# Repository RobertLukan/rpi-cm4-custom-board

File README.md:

Based on my previous projects I needed a customized RPI4 carrier board with 2 cameras input. The initial idea was taken from this project: https://www.tindie.com/products/dronecz/minimal-carrier-board-for-compute-module-4/.

I made several changes such as 4-layer PCB, added second camera lanes, differential routing for both cameras and HDMI, added temperature sensor, and added I2C and UART connectors.

I have added also two jumpers that allow disabling wireless and Bluetooth. I have tested nearly every connection. SD card connector does not work if you are using RPI4CM with emmc, otherwise, it should(not the fault of this design but the RPI design decision that I was not aware of while making this board)

In general, I am quite happy with the setup. JLCPCB manufactured and assembled most of the parts. However, one board did not have Hirose connectors soldered properly, I have received a coupon. I have not touched the spacing for Hirose connectors, but I found it may be slightly off. It is hard to connect RPI for the first time. But I don't want to modify it as it has been working for several weeks.

USB connector can be used to connect external devices. To flash a CM the dedicated jumper(OTG) needs to be connected . It is just USB2.0 and it is not delivering any power. I have tested powered USB hub/docking station and it is working fine. In this way even Ethernet connection can be used (again being limited to USB2.0)

I also created 3D-printed housing. It is my first 3d design of this type/scale, but it works. It does not have cutouts for HDMI and USB2.0 as I dont need them.

In order to use both cameras, config.txt file has to include both overlays as defined below, for my two cameras:

dtparam=i2c_arm=on

dtoverlay=imx708,cam0

dtoverlay=imx477,cam1

The majority of the connectors were assembled by JLCPCB(without I2C and camera connectors - not available at that time), I have included the production directory where all the details are attached. The positions of parts are not 100% aligned, so make sure if you are asking JLCPCB to assemble parts to align them correctly. It is very important to order the correct camera connector: https://www.digikey.at/en/products/detail/amphenol-cs-fci/SFW15R-1STAE1LF/4270877

I made several design decisions that suited my needs, such as different GPIO header connector, and 4-pin Groove connectors for UART and I2C, so they might not be suitable for your needs.

One important detail, I am powering this board with the Raspberry Pi power supply. Other power supplies with USB C connector might not work as RPI requires quite some power and I would need to implement USB PD.

Update:
I needed power(5V) for an external USB device. I knew that I could connect a powered USB docking station(hub), however, that requires yet another power supply. As I just needed to power the USB microphone, that was an overkill. I looked at my diagram and I noticed that I can take 5V from GPIO and connect one of the pins at the OTG jumper(as shown below). An important detail is that the track is not designed to carry a lot of current, so be reasonable. 

License:
Please feel free to use the design. Released under the following license: 
https://ohwr.org/cern_ohl_p_v2.txt

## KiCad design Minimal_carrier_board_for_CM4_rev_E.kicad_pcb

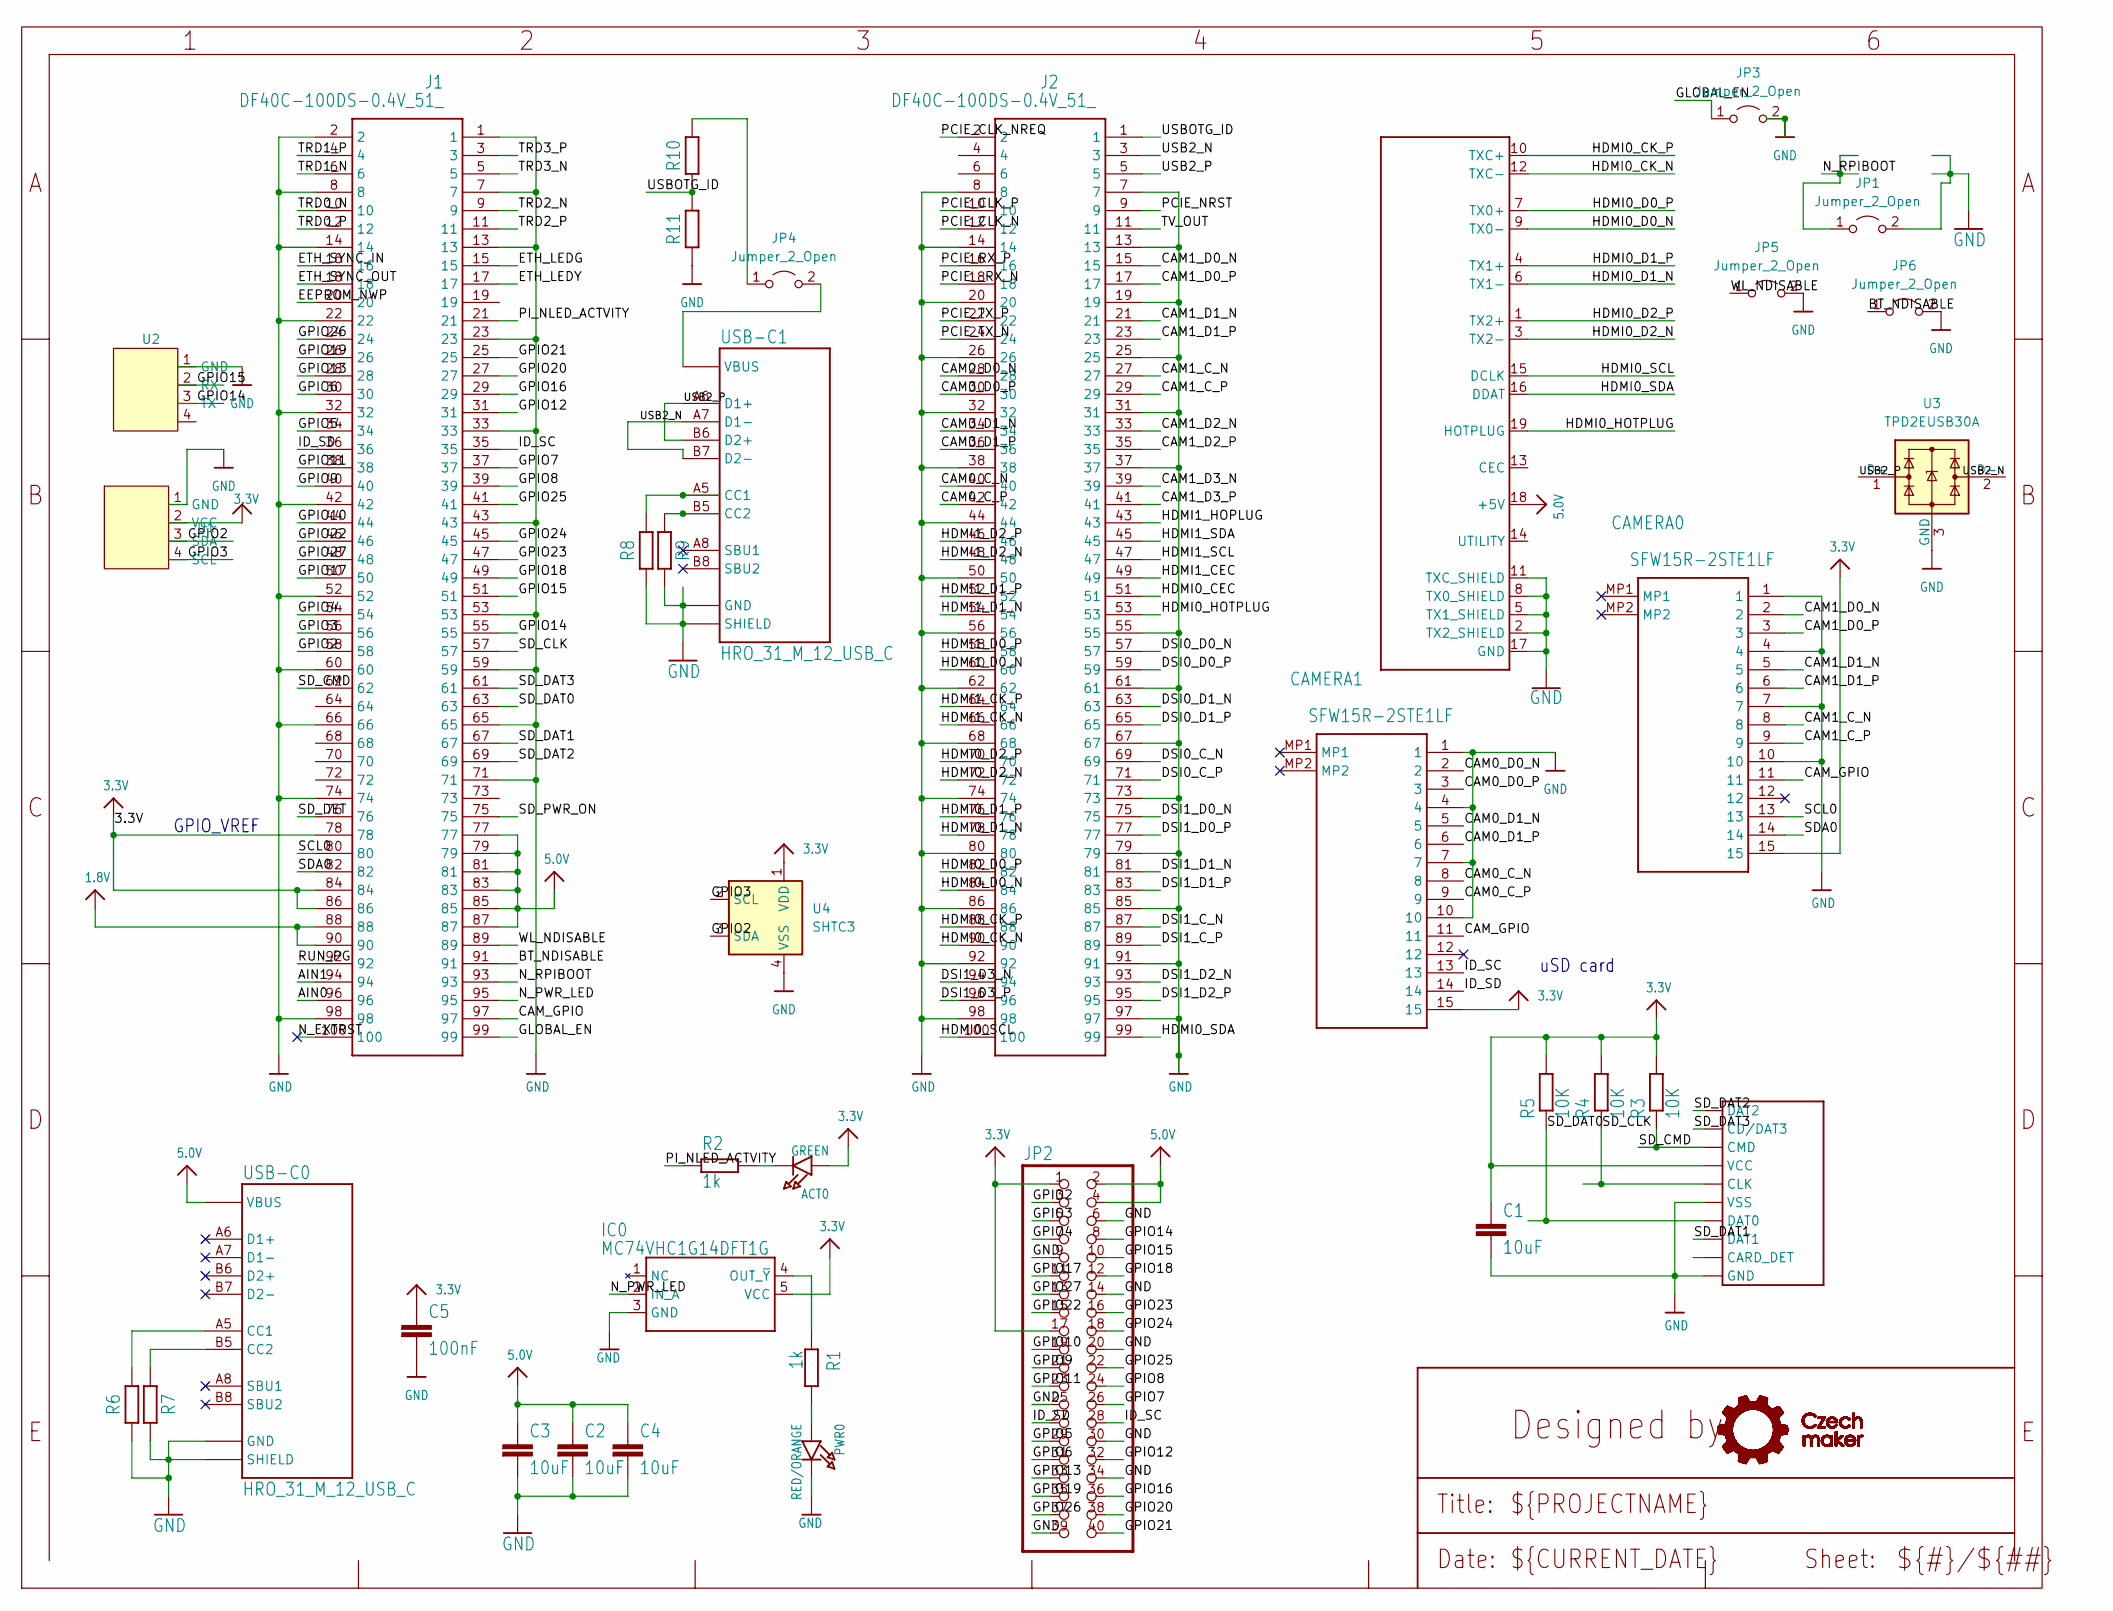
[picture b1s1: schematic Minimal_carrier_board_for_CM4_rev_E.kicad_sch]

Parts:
ACT0: GREEN; CHIPLED_0805_NOOUTLINE
C1, C2, C3, C4: 10uF; C0805
C5: 100nF; C0805
CAMERA0, CAMERA1: SFW15R-2STE1LF; SFW15R2STE1LF
HDMI0: HDMI_MOLEX_47151-0001; LCSC C428484
IC0: MC74VHC1G14DFT1G; SOT65P210X110-5N
J1: DF40C-100DS-0.4V_51_; DF40C100DS04V51; LCSC DF40C-100DS-0.4V(51)
J2: DF40C-100DS-0.4V_51_; DF40C100DS04V51
JP1, JP3, JP4, JP5, JP6: Jumper_2_Open; PinHeader_1x02_P2.54mm_Vertical
JP2: PINHD-2X20; 2X20
PWR0: RED/ORANGE; CHIPLED_0805_NOOUTLINE
R1, R2: 1k; R0805
R3, R4, R5: 10K; R0805
R6, R7, R8, R9: 5.1k; R0805
R10, R11: 2.2k; R0805
SD_CARD0: MICRO_SD_CARD_; TFP09-2--12B
U1, U2: NS-Tech_Grove_1x04_P2mm_Vertical
U3: TPD2EUSB30A; Texas_DRT-3
U4: SHTC3; Sensirion_DFN-4-1EP_2x2mm_P1mm_EP0.7x1.6mm
USB-C0, USB-C1: HRO_31_M_12_USB_C

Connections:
1.8V: J1.88, J1.90
3.3V: ACT0.A, C1.1, C5.1, CAMERA0.15, CAMERA1.15, IC0.5 (VCC), J1.78, J1.84, J1.86, JP2.1, JP2.17, R3.2, R4.2, R5.2, SD_CARD0.VCC, U1.2 (VCC), U4.1 (VDD); also elsewhere on the board
5.0V: C2.1, C3.1, C4.1, HDMI0.18 (+5V), J1.77, J1.79, J1.81, J1.83, J1.85, J1.87, JP2.2, JP2.4, USB-C0.A4 (VBUS), USB-C0.A9 (VBUS), USB-C0.B4 (VBUS), USB-C0.B9 (VBUS); also elsewhere on the board
/AIN0: J1.96
/AIN1: J1.94
/BT_NDISABLE: J1.91, JP6.1 (A)
/CAM0_C_N: CAMERA1.8, J2.40; also elsewhere on the board
/CAM0_C_P: CAMERA1.9, J2.42; also elsewhere on the board
/CAM0_D0_N: CAMERA1.2, J2.28; also elsewhere on the board
/CAM0_D0_P: CAMERA1.3, J2.30; also elsewhere on the board
/CAM0_D1_N: CAMERA1.5, J2.34; also elsewhere on the board
/CAM0_D1_P: CAMERA1.6, J2.36; also elsewhere on the board
/CAM1_C_N: CAMERA0.8, J2.27
/CAM1_C_P: CAMERA0.9, J2.29
/CAM1_D0_N: CAMERA0.2, J2.15
/CAM1_D0_P: CAMERA0.3, J2.17
/CAM1_D1_N: CAMERA0.5, J2.21
/CAM1_D1_P: CAMERA0.6, J2.23
/CAM1_D2_N: J2.33
/CAM1_D2_P: J2.35
/CAM1_D3_N: J2.39
/CAM1_D3_P: J2.41
/CAM_GPIO: CAMERA0.11, CAMERA1.11, J1.97; also elsewhere on the board
/DSI0_C_N: J2.69
/DSI0_C_P: J2.71
/DSI0_D0_N: J2.57
/DSI0_D0_P: J2.59
/DSI0_D1_N: J2.63
/DSI0_D1_P: J2.65
/DSI1_C_N: J2.87
/DSI1_C_P: J2.89
/DSI1_D0_N: J2.75
/DSI1_D0_P: J2.77
/DSI1_D1_N: J2.81
/DSI1_D1_P: J2.83
/DSI1_D2_N: J2.93
/DSI1_D2_P: J2.95
/DSI1_D3_N: J2.94
/DSI1_D3_P: J2.96
/EEPROM_NWP: J1.20
/ETH_LEDG: J1.15
/ETH_LEDY: J1.17
/ETH_SYNC_IN: J1.16
/ETH_SYNC_OUT: J1.18
/GLOBAL_EN: J1.99, JP3.1 (A)
/GPIO2: J1.58, JP2.3, U1.3 (SDA), U4.3 (SDA)
/GPIO3: J1.56, JP2.5, U1.4 (SCL), U4.2 (SCL)
/GPIO4: J1.54, JP2.7
/GPIO5: J1.34, JP2.29
/GPIO6: J1.30, JP2.31
/GPIO7: J1.37, JP2.26
/GPIO8: J1.39, JP2.24
/GPIO9: J1.40, JP2.21
/GPIO10: J1.44, JP2.19
/GPIO11: J1.38, JP2.23
/GPIO12: J1.31, JP2.32
/GPIO13: J1.28, JP2.33
/GPIO14: J1.55, JP2.8, U2.3 (TX)
/GPIO15: J1.51, JP2.10, U2.2 (RX)
/GPIO16: J1.29, JP2.36
/GPIO17: J1.50, JP2.11
/GPIO18: J1.49, JP2.12
/GPIO19: J1.26, JP2.35
/GPIO20: J1.27, JP2.38
/GPIO21: J1.25, JP2.40
/GPIO22: J1.46, JP2.15
/GPIO23: J1.47, JP2.16
/GPIO24: J1.45, JP2.18
/GPIO25: J1.41, JP2.22
/GPIO26: J1.24, JP2.37
/GPIO27: J1.48, JP2.13
/HDMI0_CEC: J2.51
/HDMI0_CK_N: HDMI0.12 (TXC-), J2.90
/HDMI0_CK_P: HDMI0.10 (TXC+), J2.88
/HDMI0_D0_N: HDMI0.9 (TX0-), J2.84
/HDMI0_D0_P: HDMI0.7 (TX0+), J2.82
/HDMI0_D1_N: HDMI0.6 (TX1-), J2.78
/HDMI0_D1_P: HDMI0.4 (TX1+), J2.76
/HDMI0_D2_N: HDMI0.3 (TX2-), J2.72
/HDMI0_D2_P: HDMI0.1 (TX2+), J2.70
/HDMI0_HOTPLUG: HDMI0.19 (HOTPLUG), J2.53
/HDMI0_SCL: HDMI0.15 (DCLK), J2.100
/HDMI0_SDA: HDMI0.16 (DDAT), J2.99
/HDMI1_CEC: J2.49
/HDMI1_CK_N: J2.66
/HDMI1_CK_P: J2.64
/HDMI1_D0_N: J2.60
/HDMI1_D0_P: J2.58
/HDMI1_D1_N: J2.54
/HDMI1_D1_P: J2.52
/HDMI1_D2_N: J2.48
/HDMI1_D2_P: J2.46
/HDMI1_HOPLUG: J2.43
/HDMI1_SCL: J2.47
/HDMI1_SDA: J2.45
/ID_SC: CAMERA1.13, J1.35, JP2.28; also elsewhere on the board
/ID_SD: CAMERA1.14, J1.36, JP2.27; also elsewhere on the board
/N_EXTRST: J1.100
/N_PWR_LED: IC0.2 (IN_A), J1.95
/N_RPIBOOT: J1.93, JP1.1 (A)
/PCIE_CLK_N: J2.12
/PCIE_CLK_NREQ: J2.2
/PCIE_CLK_P: J2.10
/PCIE_NRST: J2.9
/PCIE_RX_P: J2.16
/PCIE_TX_N: J2.24
/PCIE_TX_P: J2.22
/PCIE__RX_N: J2.18
/PI_NLED_ACTVITY: J1.21, R2.1
/RUN_PG: J1.92
/SCL0: CAMERA0.13, J1.80
/SDA0: CAMERA0.14, J1.82
/SD_CLK: J1.57, R4.1, SD_CARD0.CLK
/SD_CMD: J1.62, R3.1, SD_CARD0.CMD
/SD_DAT0: J1.63, R5.1, SD_CARD0.DAT0
/SD_DAT1: J1.67, SD_CARD0.DAT1
/SD_DAT2: J1.69, SD_CARD0.DAT2
/SD_DAT3: J1.61, SD_CARD0.CD/DAT3
/SD_DET: J1.76
/SD_PWR_ON: J1.75
/TRD0_N: J1.10
/TRD0_P: J1.12
/TRD1_N: J1.6
/TRD1_P: J1.4
/TRD2_N: J1.9
/TRD2_P: J1.11
/TRD3_N: J1.5
/TRD3_P: J1.3
/TV_OUT: J2.11
/USB2_N: J2.3, U3.2 (D-), USB-C1.A7 (D1-), USB-C1.B7 (D2-); also elsewhere on the board
/USB2_P: J2.5, U3.1 (D+), USB-C1.A6 (D1+), USB-C1.B6 (D2+); also elsewhere on the board
/USBOTG_ID: J2.1, R10.1, R11.2
/WL_NDISABLE: J1.89, JP5.1 (A)
GND: C1.2, C2.2, C3.2, C4.2, C5.2, CAMERA0.1, CAMERA0.4, CAMERA0.7, CAMERA0.10, CAMERA1.1, CAMERA1.4, CAMERA1.7, CAMERA1.10, HDMI0.2 (TX2_SHIELD), HDMI0.5 (TX1_SHIELD), HDMI0.8 (TX0_SHIELD), HDMI0.11 (TXC_SHIELD), HDMI0.17 (GND), IC0.3 (GND), J1.1, J1.2, J1.7, J1.8, J1.13, J1.14, J1.22, J1.23, J1.32, J1.33, J1.42, J1.43, J1.52, J1.53, J1.59, J1.60, J1.65, J1.66, J1.71, J1.74, J1.98, J2.7, J2.8, J2.13, J2.14, J2.19, J2.20, J2.25, J2.26, J2.31, J2.32, J2.37, J2.38, J2.44, J2.50, J2.55, J2.56, J2.61, J2.62, J2.67, J2.68, J2.73, J2.74, J2.79, J2.80, J2.85, J2.86, J2.91, J2.92, J2.97, J2.98, JP1.2 (B), JP2.6, JP2.9, JP2.14, JP2.20, JP2.25, JP2.30, JP2.34, JP2.39, JP3.2 (B), JP5.2 (B), JP6.2 (B), PWR0.C, R6.1, R7.2, R8.1, R9.2, R11.1, SD_CARD0.GND, SD_CARD0.GND@1 (GND), SD_CARD0.GND@2 (GND), SD_CARD0.GND@3 (VSS), SD_CARD0.VSS (GND), U1.1 (GND), U2.1 (GND), U3.3 (GND), U4.4 (VSS), USB-C0.A1 (GND), USB-C0.A12 (GND), USB-C0.B1 (GND), USB-C0.B12 (GND), USB-C0.S1 (SHIELD), USB-C0.S2 (SHIELD), USB-C0.S3 (SHIELD), USB-C0.S4 (SHIELD), USB-C1.A1 (GND), USB-C1.A12 (GND), USB-C1.B1 (GND), USB-C1.B12 (GND), USB-C1.S1 (SHIELD), USB-C1.S2 (SHIELD), USB-C1.S3 (SHIELD), USB-C1.S4 (SHIELD); also elsewhere on the board
unnamed: ACT0.C, R2.2
unnamed: IC0.4 (OUT_~Y), R1.1
unnamed: JP4.1 (A), R10.2
unnamed 137: JP4.2 (B), USB-C1.A4 (VBUS), USB-C1.A9 (VBUS), USB-C1.B4 (VBUS), USB-C1.B9 (VBUS); also elsewhere on the board
unnamed: PWR0.A, R1.2
unnamed 139: R6.2, USB-C0.A5 (CC1); also elsewhere on the board
unnamed 140: R7.1, USB-C0.B5 (CC2); also elsewhere on the board
unnamed 141: R8.2, USB-C1.A5 (CC1); also elsewhere on the board
unnamed 142: R9.1, USB-C1.B5 (CC2); also elsewhere on the board

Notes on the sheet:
uSD card
GPIO_VREF

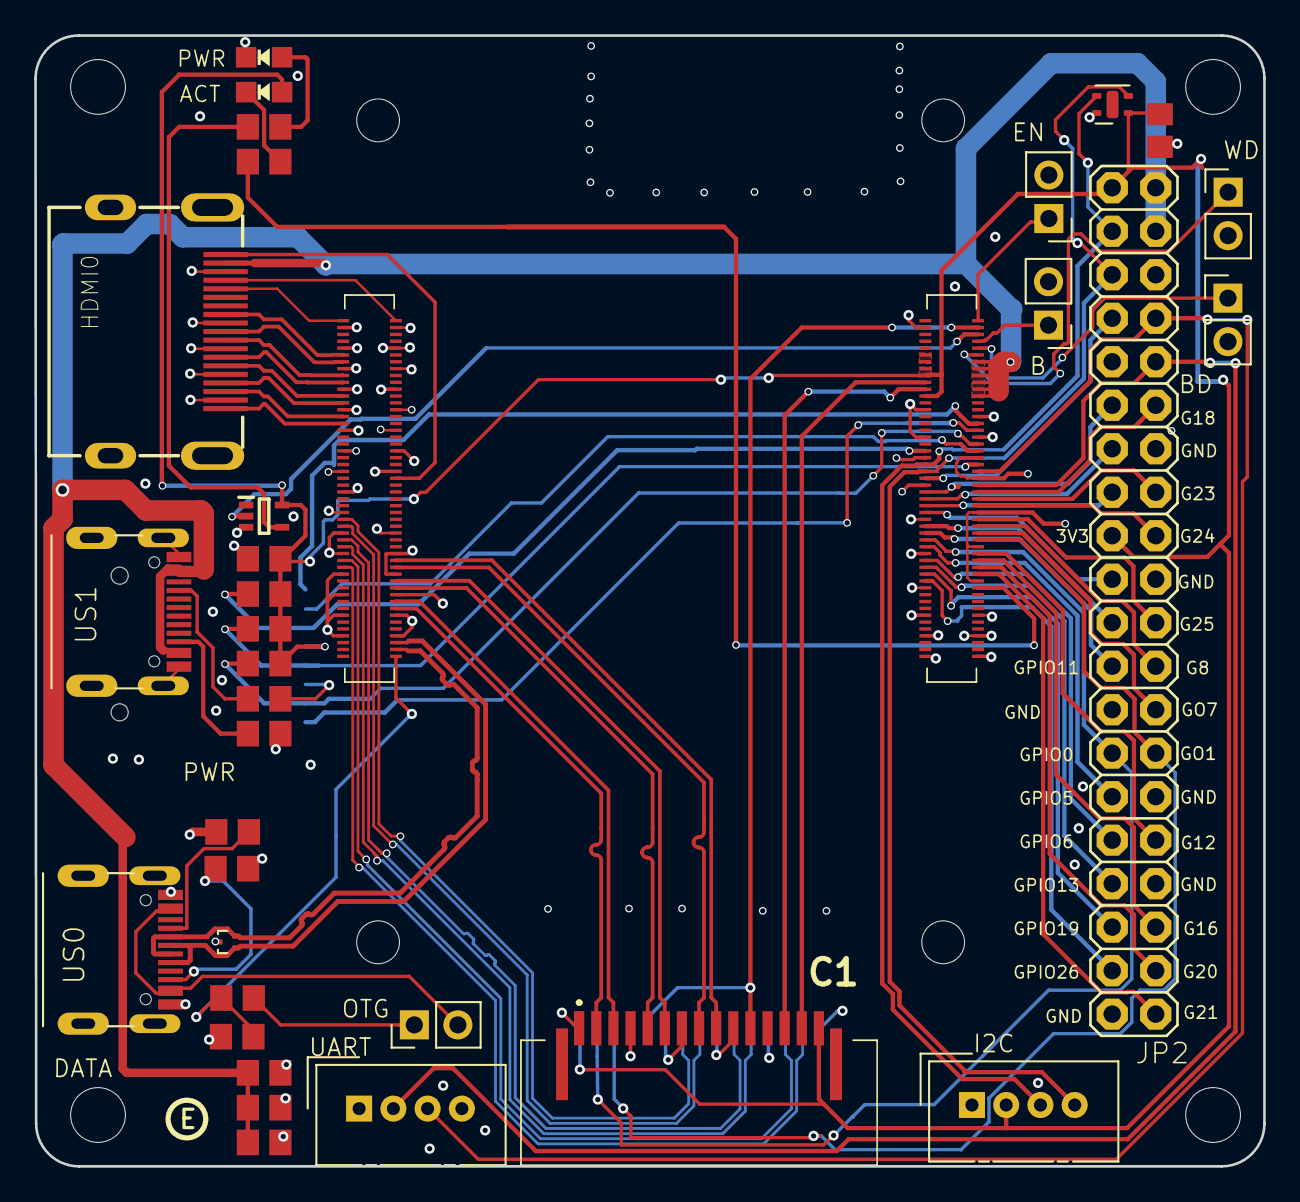
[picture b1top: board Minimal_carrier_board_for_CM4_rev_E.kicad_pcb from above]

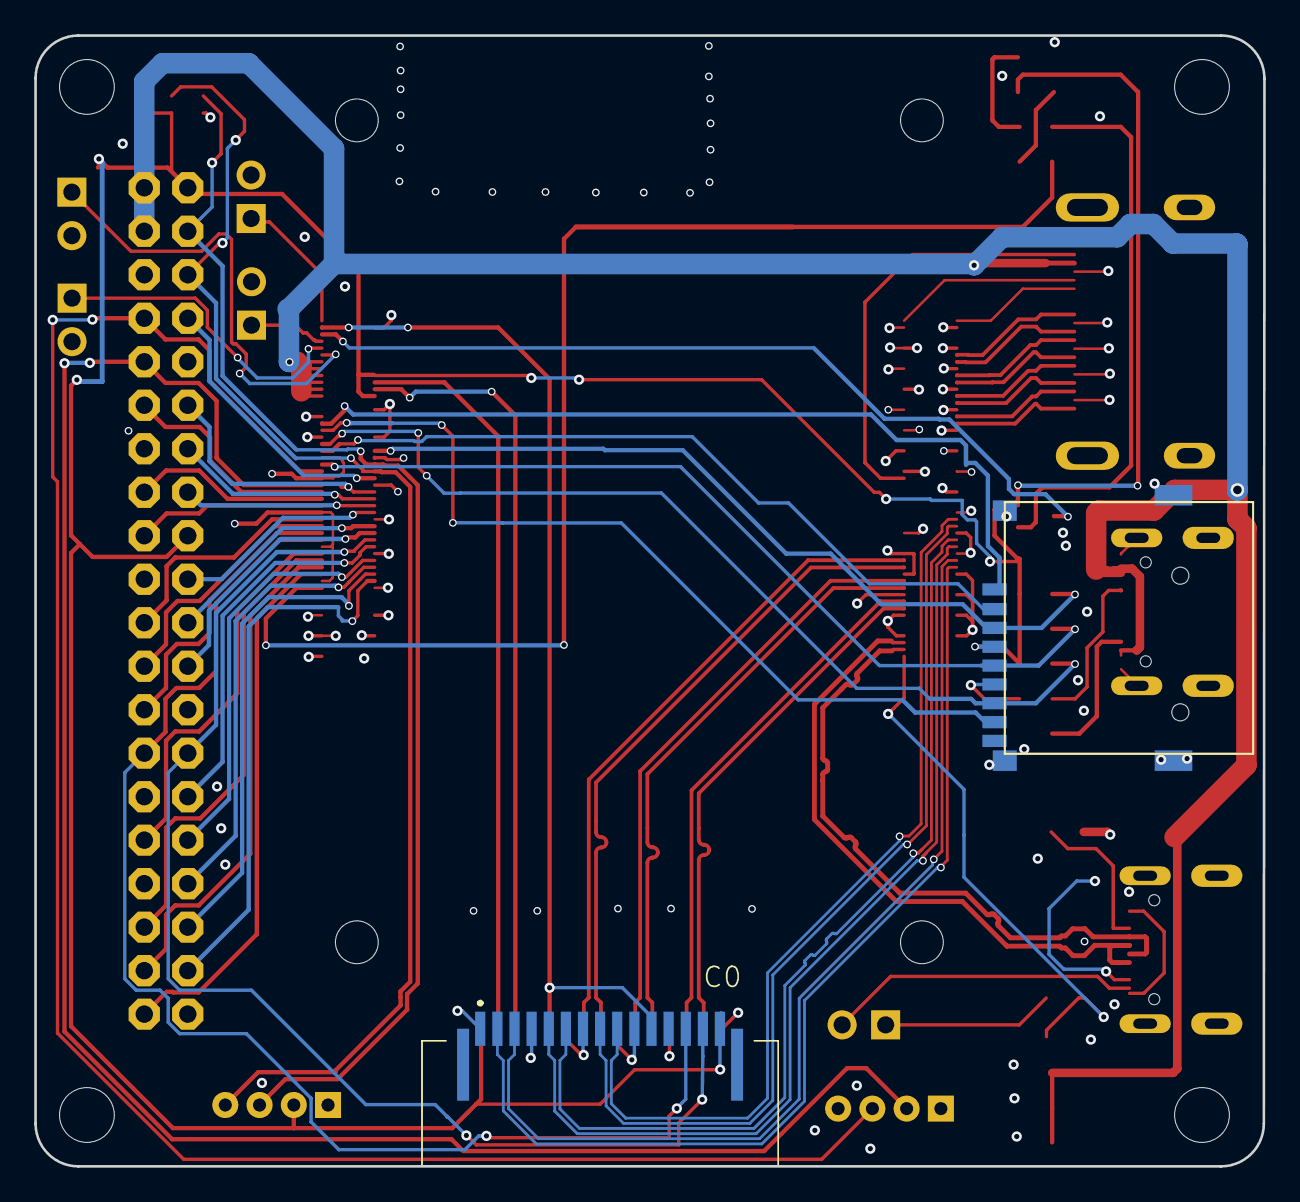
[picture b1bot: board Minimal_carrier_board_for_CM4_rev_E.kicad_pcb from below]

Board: 4 copper layers, 71.8 x 66.0 mm, 45 parts (2 on the bottom side), 82 nets.

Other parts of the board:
@HOLE0, @HOLE1, @HOLE2, @HOLE3, @HOLE4, @HOLE5, @HOLE6, @HOLE7: (no value)
C0: SFW15R-2STE1LF; SFW15R2STE1LF
US0, US1: HRO_31_M_12_USB_C

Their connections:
3.3V: C0.15; also elsewhere on the board
5.0V: US1.A4 (VBUS), US1.A9 (VBUS), US1.B4 (VBUS), US1.B9 (VBUS); also elsewhere on the board
/CAM0_C_N: C0.8; also elsewhere on the board
/CAM0_C_P: C0.9; also elsewhere on the board
/CAM0_D0_N: C0.2; also elsewhere on the board
/CAM0_D0_P: C0.3; also elsewhere on the board
/CAM0_D1_N: C0.5; also elsewhere on the board
/CAM0_D1_P: C0.6; also elsewhere on the board
/CAM_GPIO: C0.11; also elsewhere on the board
/ID_SC: C0.13; also elsewhere on the board
/ID_SD: C0.14; also elsewhere on the board
/USB2_N: US0.A7 (D1-), US0.B7 (D2-); also elsewhere on the board
/USB2_P: US0.A6 (D1+), US0.B6 (D2+); also elsewhere on the board
GND: C0.1, C0.4, C0.7, C0.10, US0.A1 (GND), US0.A12 (GND), US0.B1 (GND), US0.B12 (GND), US0.S1 (SHIELD), US0.S2 (SHIELD), US0.S3 (SHIELD), US0.S4 (SHIELD), US1.A1 (GND), US1.A12 (GND), US1.B1 (GND), US1.B12 (GND), US1.S1 (SHIELD), US1.S2 (SHIELD), US1.S3 (SHIELD), US1.S4 (SHIELD); also elsewhere on the board
unnamed 137: US0.A4 (VBUS), US0.A9 (VBUS), US0.B4 (VBUS), US0.B9 (VBUS); also elsewhere on the board
unnamed 139: US1.A5 (CC1); also elsewhere on the board
unnamed 140: US1.B5 (CC2); also elsewhere on the board
unnamed 141: US0.A5 (CC1); also elsewhere on the board
unnamed 142: US0.B5 (CC2); also elsewhere on the board

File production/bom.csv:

Designator,Footprint,Quantity,Value,LCSC Part #
"@HOLE0, @HOLE1, @HOLE2, @HOLE3, @HOLE4, @HOLE5, @HOLE6, @HOLE7",,8,,
ACT0,CHIPLED_0805_NOOUTLINE,1,GREEN,
"C0, CAMERA0",SFW15R2STE1LF,2,SFW15R-2STE1LF,
"C1, C2, C3, C4",C0805,4,10uF,
C5,C0805,1,100nF,
HDMI0,HDMI_MOLEX_47151-0001,1,HDMI_MOLEX_47151-0001,C428484
IC0,SOT65P210X110-5N,1,MC74VHC1G14DFT1G,
"J1, J2",DF40C100DS04V51,2,DF40C-100DS-0.4V_51_,DF40C-100DS-0.4V(51)
"JP1, JP3, JP4, JP5, JP6",PinHeader_1x02_P2.54mm_Vertical,5,Jumper_2_Open,
JP2,2X20,1,PINHD-2X20,
PWR0,CHIPLED_0805_NOOUTLINE,1,RED/ORANGE,
"R1, R2",R0805,2,1k,
"R10, R11",R0805,2,2.2k,
"R3, R4, R5",R0805,3,10K,
"R6, R7, R8, R9",R0805,4,5.1k,
SD_CARD0,TFP09-2--12B,1,MICRO_SD_CARD_,
"U1, U2",NS-Tech_Grove_1x04_P2mm_Vertical,2,~,
U3,Texas_DRT-3,1,TPD2EUSB30A,
U4,Sensirion_DFN-4-1EP_2x2mm_P1mm_EP0.7x1.6mm,1,SHTC3,
"US0, US1",HRO_31_M_12_USB_C,2,HRO_31_M_12_USB_C,

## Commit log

2024-01-08 Add files via upload
    Initial upload
